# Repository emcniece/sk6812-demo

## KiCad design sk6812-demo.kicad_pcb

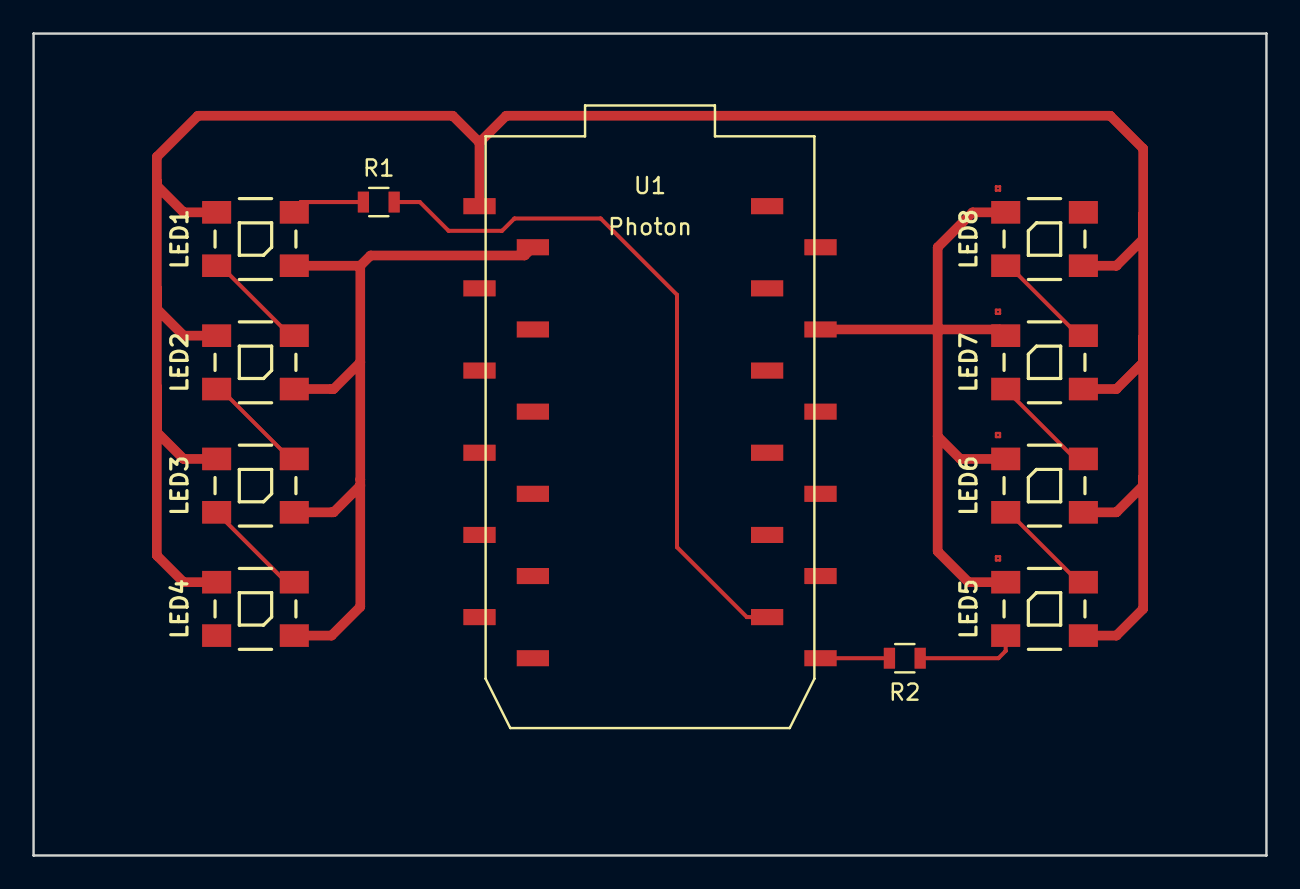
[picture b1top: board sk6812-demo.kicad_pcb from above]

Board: 2 copper layers, 76.2 x 50.8 mm, 11 parts (0 on the bottom side), 12 nets.

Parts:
LED1, LED2, LED3, LED4: WS2812B
LED5, LED6, LED7, LED8: SK6812
R1, R2: R; R_0805
U1: Photon; photon-smt-headers

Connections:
+5V: LED1.1, LED2.1, LED3.1, LED4.1, LED5.3, LED6.3, LED7.3, LED8.3, U1.1
GND: LED1.3, LED2.3, LED3.3, LED4.3, LED5.1, LED6.1, LED7.1, LED8.1, U1.2, U1.21
unnamed: LED1.2, LED2.4
unnamed: LED1.4, R1.1
unnamed: LED2.2, LED3.4
unnamed: LED3.2, LED4.4
unnamed: LED5.2, R2.1
unnamed: LED5.4, LED6.2
unnamed: LED6.4, LED7.2
unnamed: LED7.4, LED8.2
unnamed: R1.2, U1.14
unnamed: R2.2, U1.13

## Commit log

2016-12-01 init
2016-12-02 Fixing power nets
